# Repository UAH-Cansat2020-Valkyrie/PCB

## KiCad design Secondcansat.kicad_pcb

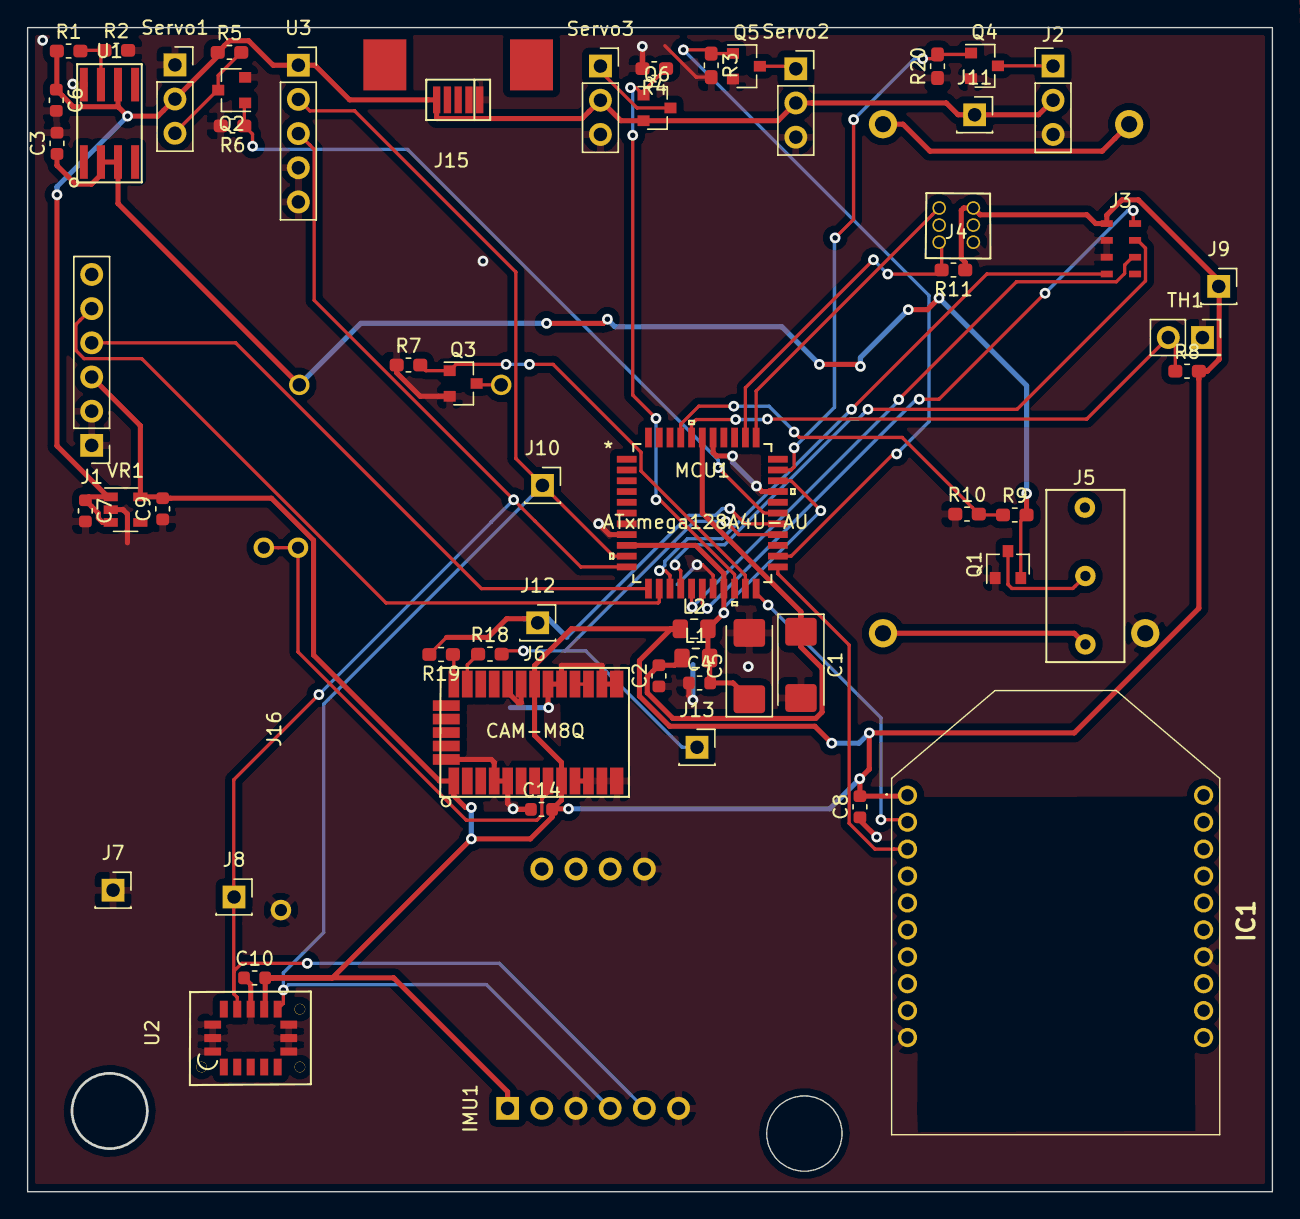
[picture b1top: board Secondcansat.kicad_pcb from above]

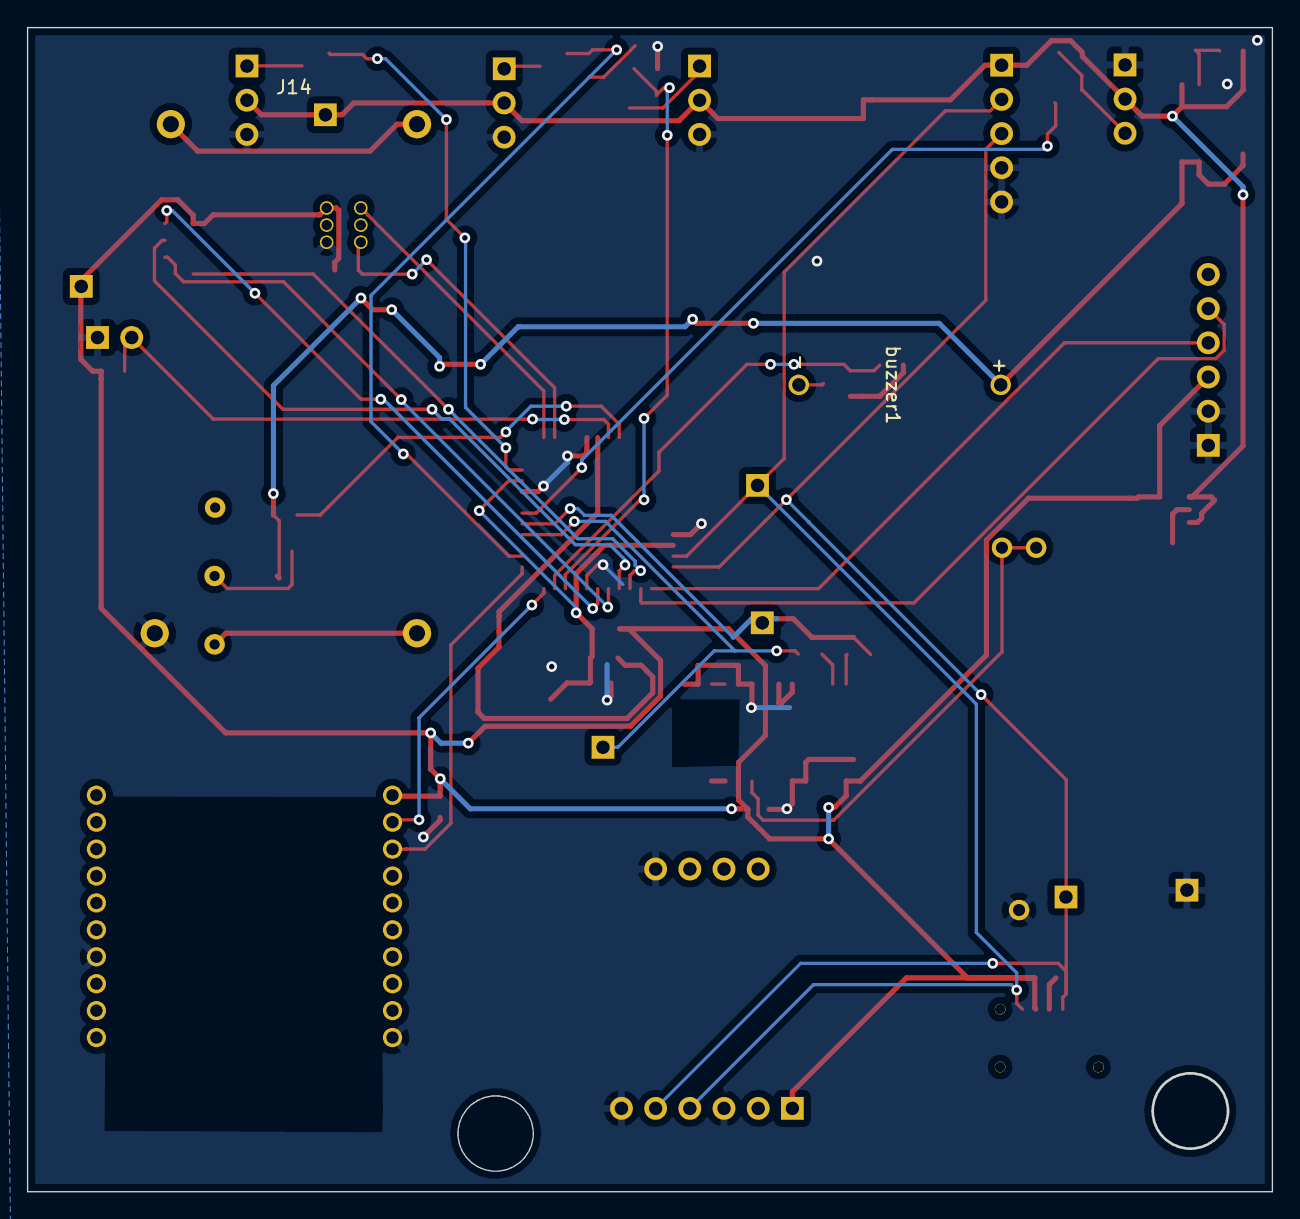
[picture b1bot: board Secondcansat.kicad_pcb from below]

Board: 2 copper layers, 92.4 x 86.4 mm, 61 parts (2 on the bottom side), 40 nets.

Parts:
C1, C5: 10uF; CP_EIA-6032-15_Kemet-U
C2, C4, C10: 100nF; C_0603_1608Metric
C3, C14: 5uF; C_0603_1608Metric
C6: 10uF; C_0603_1608Metric
C7, C8: 1uF; C_0603_1608Metric
C9: 50uF; C_0603_1608Metric
IC1: XBP9B-XCWT-001; XBP9BXCWT001
IMU1: BN0055breakout; BNO055breakout
J1: OpenlogBreakout; PinHeader_1x06_P2.54mm_Vertical
J2: Camera; PinHeader_1x03_P2.54mm_Vertical
J3: Pressure_MS5607; pressure_MS5607
J4: Debugger; PDI connector
J5: RBF; RBF_SS0750301F020P1A
J6: CAM-M8Q-GPS; CAM-M8Q
J7: GND; PinSocket_1x01_P2.54mm_Vertical
J8: SCL; PinSocket_1x01_P2.54mm_Vertical
J9: 3v; PinSocket_1x01_P2.54mm_Vertical
J10: SDA; PinSocket_1x01_P2.54mm_Vertical
J11: 5V; PinSocket_1x01_P2.54mm_Vertical
J12: Tx; PinSocket_1x01_P2.54mm_Vertical
J13: Rx; PinSocket_1x01_P2.54mm_Vertical
J14: Battery_Holder_keystone 1079; BatteryHolder
J15: USB_B_Mini; USB-Mini
J16: coinBattery; coin_Battery_120591-1
L1, L2: 10uH; L_0805_2012Metric_Pad1.15x1.40mm_HandSolder
MCU1: ATxmega128A4U-AU; ATXMEGA128A4U-AU
Q1: Q_PMOS_DMG2305UX-13DIDKR-ND; SOT-23_PMOS
Q2, Q3, Q4, Q5, Q6: Q_NMOS_BSS138; SOT-23_PMOS
R1: 274kohm; R_0603_1608Metric_Pad1.05x0.95mm_HandSolder
R2: 30Kohm; R_0603_1608Metric_Pad1.05x0.95mm_HandSolder
R3, R4, R5, R6, R7, R11, R20: 10kohm; R_0603_1608Metric_Pad1.05x0.95mm_HandSolder
R8, R10: 2kohm; R_0603_1608Metric_Pad1.05x0.95mm_HandSolder
R9: 5kohm; R_0603_1608Metric_Pad1.05x0.95mm_HandSolder
R18, R19: 220ohm; R_0603_1608Metric_Pad1.05x0.95mm_HandSolder
Servo1, Servo2: Servo_Adafruit_FS90R; PinSocket_1x03_P2.54mm_Vertical
Servo3: Servo_Adafruit_SG92R; PinSocket_1x03_P2.54mm_Vertical
TH1: Therm_NXRT15WB473FA3A016; PinSocket_2x01_P2.54mm_Vertical
U1: VR_TPS7A7001DDAR
U2: SAir_Speed_DP32-125PA-TR-250PCS; Diff_Press
U3: SPS30; PinSocket_1x05_P2.54mm_Vertical
VR1: VR__TLV75533PDBVR; Vreg3.3
buzzer1: buzzer_MAS803Q; Buzzer

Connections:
+3V3: C8.2, C9.2, C10.2, C14.2, IC1.1, IMU1.1, J1.3, J3.1, J4.2, J6.1, J6.9, J6.20, J9.1, L2.1, R8.2, R11.1, U2.7, VR1.5
+5V: C6.1, C7.1, J2.2, J11.1, J15.1, Q6.3, R1.1, R5.1, Servo1.2, Servo2.2, Servo3.2, U1.6, U3.1, VR1.1, VR1.3
+6V: C3.1, Q1.3, R9.2, U1.2, U1.3, buzzer1.2
ADC_A1: MCU1.41, R9.1, R10.2
Buzzer: MCU1.21, Q3.2, R7.2
CSB: J3.4, MCU1.14
GND: C1.2, C2.1, C3.2, C4.1, C5.2, C6.2, C7.2, C8.1, C9.1, C10.1, C14.1, IC1.10, IC1.14, IMU1.3, IMU1.6, IMU1.10, J1.1, J1.2, J2.3, J3.2, J3.3, J4.6, J6.4, J6.5, J6.10, J6.11, J6.12, J6.13, J6.14, J6.15, J6.18, J6.19, J6.21, J6.22, J6.31, J7.1, J14.3, J15.5, J16.1, MCU1.8, MCU1.18, MCU1.30, MCU1.38, Q1.2, Q2.3, Q3.3, Q4.3, Q5.3, R2.2, R3.2, R4.2, R6.2, R7.1, R10.1, R20.1, Servo1.1, Servo2.3, Servo3.3, TH1.1, U1.8, U2.1, U2.2, U2.3, U2.6, U2.9, U2.10, U2.11, U3.4, U3.5, VR1.2
MCUAVCC: C1.1, C2.2, L1.1, MCU1.39
MCUVCC: C4.2, C5.1, L1.2, L2.2, MCU1.9, MCU1.19, MCU1.31
MISO: J3.6, MCU1.16
MOSI: J3.7, MCU1.15
unnamed: J2.1, Q4.1
unnamed: J5.2, Q1.1
unnamed: J6.16, J6.17
unnamed: J6.25, R18.1
unnamed: J6.26, R19.1
unnamed: J14.1, J14.2
unnamed: J5.1, J14.4
unnamed: J6.8, J16.2, J16.3
unnamed: Q2.1, R5.2, Servo1.3
unnamed: Q3.1, buzzer1.1
unnamed: Q5.1, Servo2.1
unnamed: Q6.1, Servo3.1
unnamed: R1.2, R2.1, U1.7
PDICLK: J4.5, MCU1.35, R11.2
PDIDATA: J4.1, MCU1.34
PWM: MCU1.28, Q2.2, R6.1
RX_PD2: IC1.2, MCU1.22
RX_PD6: J13.1, MCU1.26, R18.2
SCL: IMU1.5, J8.1, MCU1.11, U2.5, U3.3
SCLK: J3.8, MCU1.17
SDA: IMU1.4, J10.1, MCU1.10, U2.8, U3.2
TCD1: MCU1.24, Q5.2, R3.1
TC_PD0: MCU1.20, Q6.2, R4.1
TX_PD3: IC1.3, MCU1.23
TX_PD7: J12.1, MCU1.27, R19.2
Therm_ADCA0: MCU1.40, R8.1, TH1.2
USART_RX_PC2: J1.4, MCU1.12
USART_TX_PC3: J1.5, MCU1.13
cameraon: MCU1.32, Q4.2, R20.2

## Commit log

2019-11-02 Initial comit
2019-11-08 added particle sensor
2019-11-08 Wired up I2C sensors
2019-11-08 made pressure footprint
2019-11-08 pressure sensor footprint
2019-11-29 footprints for pmos and 5VR
2019-11-30 Differential pressure sensor
2019-12-18 made footprints
2020-01-14 Did some stuff
2020-01-17 some footprints
2020-01-18 Did pcb
2020-01-27 reversed source and drain in the Pchannel mosfet

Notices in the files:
parts and their libraries:
Copyright 2016 Accelerated Designs. All rights reserved.
